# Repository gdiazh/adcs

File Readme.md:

Project: ADCS for SUCHAI CubeSat
--------------------------------------

# Overview

The drivers and interface for SUCHAI CubeSat.

# Content

-[sw]

--[Drivers](#drivers)

--[Interface](#interface)

--[Firmware](#firmware)

-[hw]()

-[Eagle](#eagle)

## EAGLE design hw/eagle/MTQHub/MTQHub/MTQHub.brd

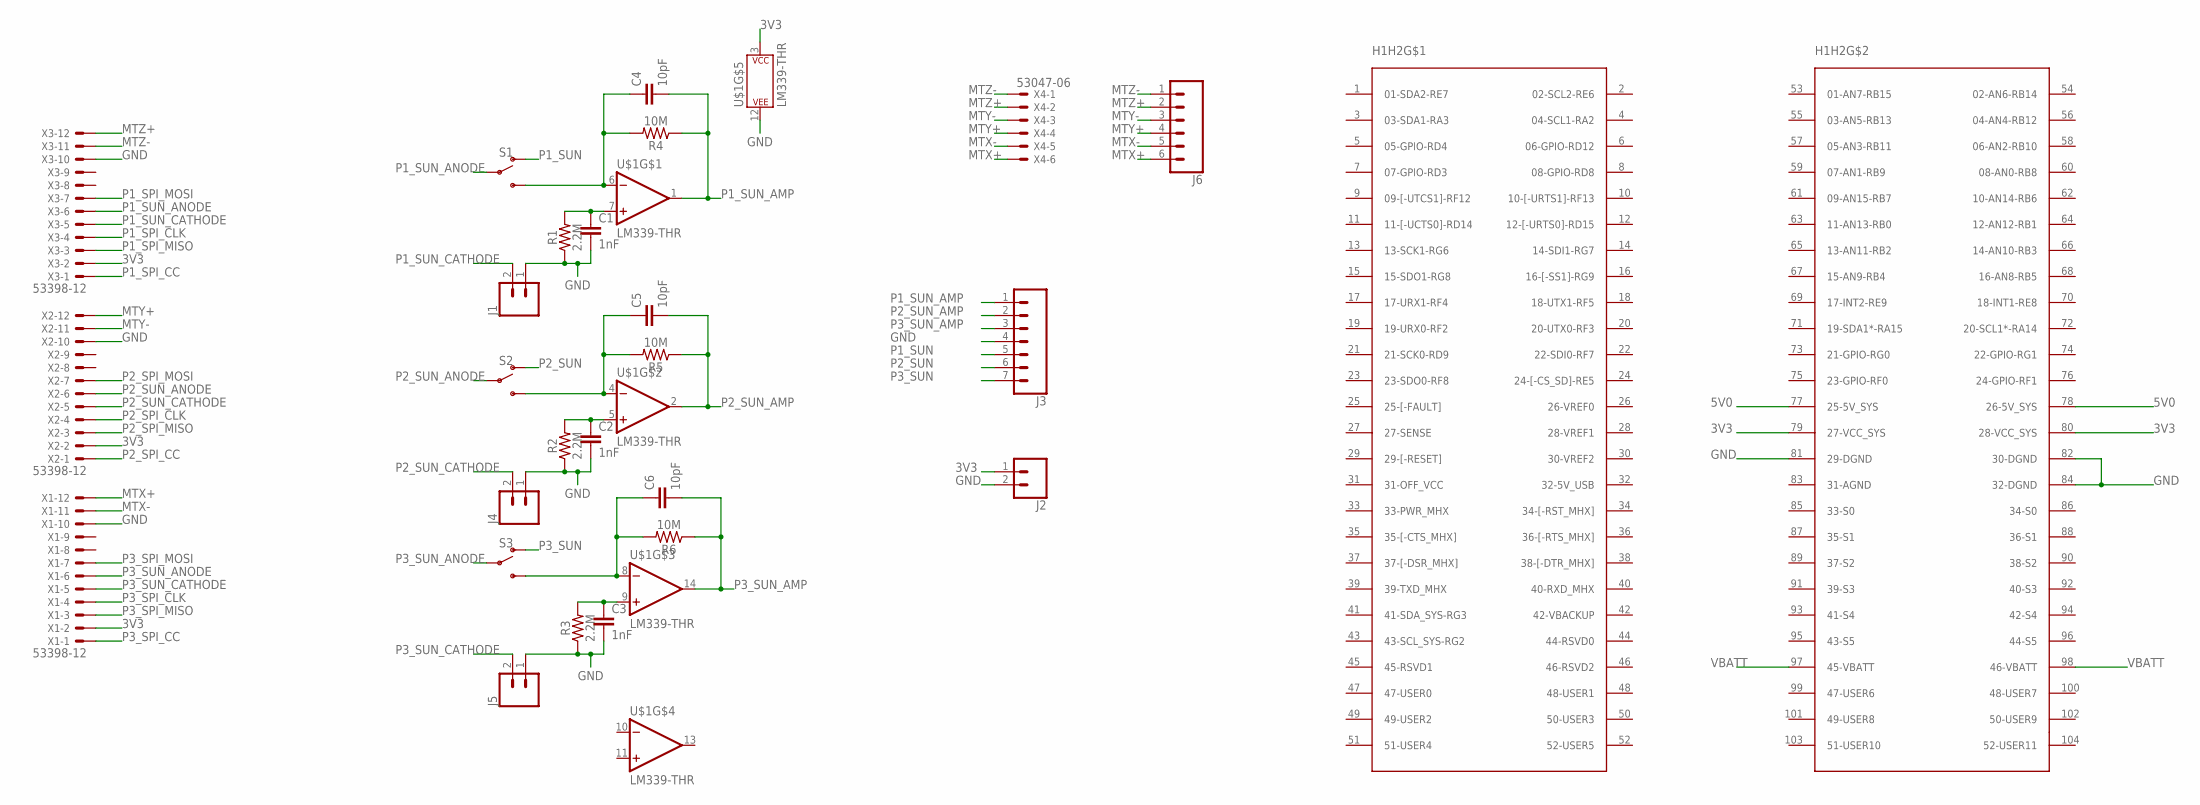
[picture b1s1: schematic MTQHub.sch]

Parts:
C1, C2, C3: 1nF; 0603
C4, C5, C6: 10pF; 0603
H1H2: PC104_CONN; PC_104
J1, J2, J4, J5: CONN_02; 1X02
J3: CONN_07; 1X07
J6: CONN_06SILK_FEMALE_PTH; 1X06
R1, R2, R3: 2.2M; 0603
R4, R5, R6: 10M; 0603
S1, S2, S3: SWITCH-SPDT-PTH-11.6X4.0MM; SWITCH_SPDT_PTH_11.6X4.0MM
U$1: LM339-THR; DIL14
X1, X2, X3: 53398-12
X4: 53047-06

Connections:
3V3: H1H2.79 (27-VCC_SYS), H1H2.80 (28-VCC_SYS), J2.1, U$1.3 (P$V+), X1.2, X2.2, X3.2
5V0: H1H2.77 (25-5V_SYS), H1H2.78 (26-5V_SYS)
GND: C1.2, C2.2, C3.2, H1H2.81 (29-DGND), H1H2.82 (30-DGND), H1H2.84 (32-DGND), J1.1, J2.2, J3.4, J4.1, J5.1, R1.1, R2.1, R3.1, U$1.12 (P$V-), X1.10, X2.10, X3.10
MTX+: J6.6, X1.12, X4.6
MTX-: J6.5, X1.11, X4.5
MTY+: J6.4, X2.12, X4.4
MTY-: J6.3, X2.11, X4.3
MTZ+: J6.2, X3.12, X4.2
MTZ-: J6.1, X3.11, X4.1
unnamed: C1.1, R1.2, U$1.7 (+IN)
unnamed: C2.1, R2.2, U$1.5 (+IN)
unnamed: C3.1, R3.2, U$1.9 (+IN)
unnamed: C4.1, R4.2, S1.3 (S), U$1.6 (-IN)
unnamed: C5.1, R5.2, S2.3 (S), U$1.4 (-IN)
unnamed: C6.1, R6.2, S3.3 (S), U$1.8 (-IN)
P1_SPI_CC: X3.1
P1_SPI_CLK: X3.4
P1_SPI_MISO: X3.3
P1_SPI_MOSI: X3.7
P1_SUN: J3.5, S1.1 (O)
P1_SUN_AMP: C4.2, J3.1, R4.1, U$1.1 (OUT)
P1_SUN_ANODE: S1.2, X3.6
P1_SUN_CATHODE: J1.2, X3.5
P2_SPI_CC: X2.1
P2_SPI_CLK: X2.4
P2_SPI_MISO: X2.3
P2_SPI_MOSI: X2.7
P2_SUN: J3.6, S2.1 (O)
P2_SUN_AMP: C5.2, J3.2, R5.1, U$1.2 (OUT)
P2_SUN_ANODE: S2.2, X2.6
P2_SUN_CATHODE: J4.2, X2.5
P3_SPI_CC: X1.1
P3_SPI_CLK: X1.4
P3_SPI_MISO: X1.3
P3_SPI_MOSI: X1.7
P3_SUN: J3.7, S3.1 (O)
P3_SUN_AMP: C6.2, J3.3, R6.1, U$1.14 (OUT)
P3_SUN_ANODE: S3.2, X1.6
P3_SUN_CATHODE: J5.2, X1.5
VBATT: H1H2.97 (45-VBATT), H1H2.98 (46-VBATT)

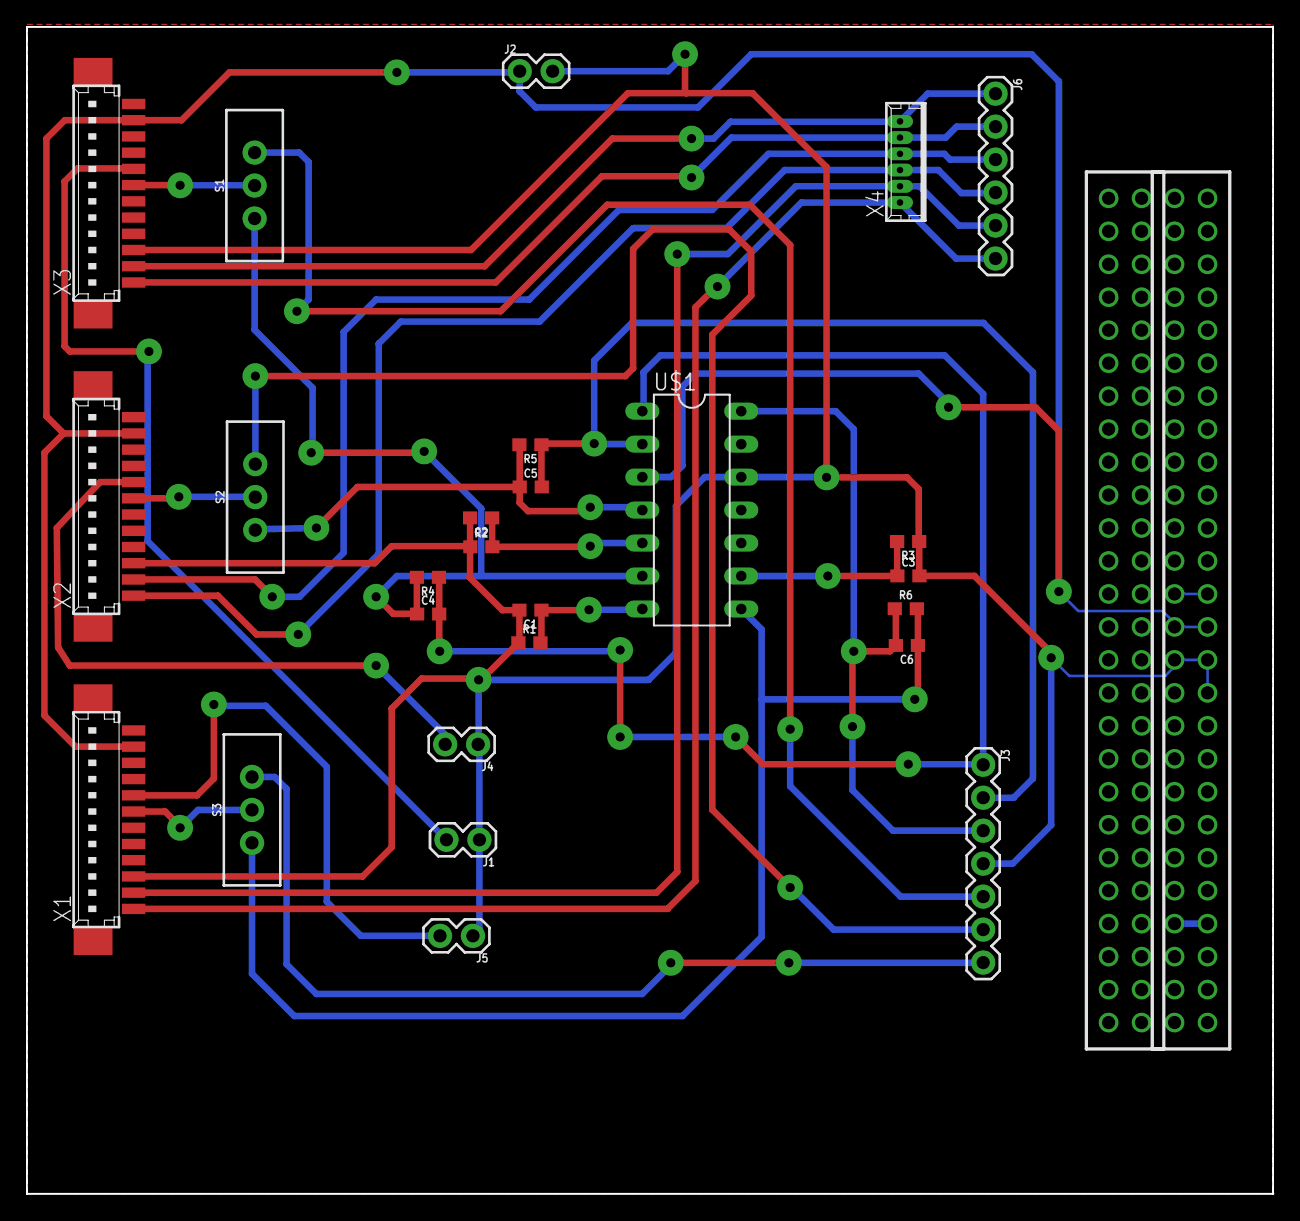
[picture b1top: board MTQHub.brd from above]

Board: 2 copper layers, 96.0 x 89.9 mm, 27 parts (0 on the bottom side), 28 nets.

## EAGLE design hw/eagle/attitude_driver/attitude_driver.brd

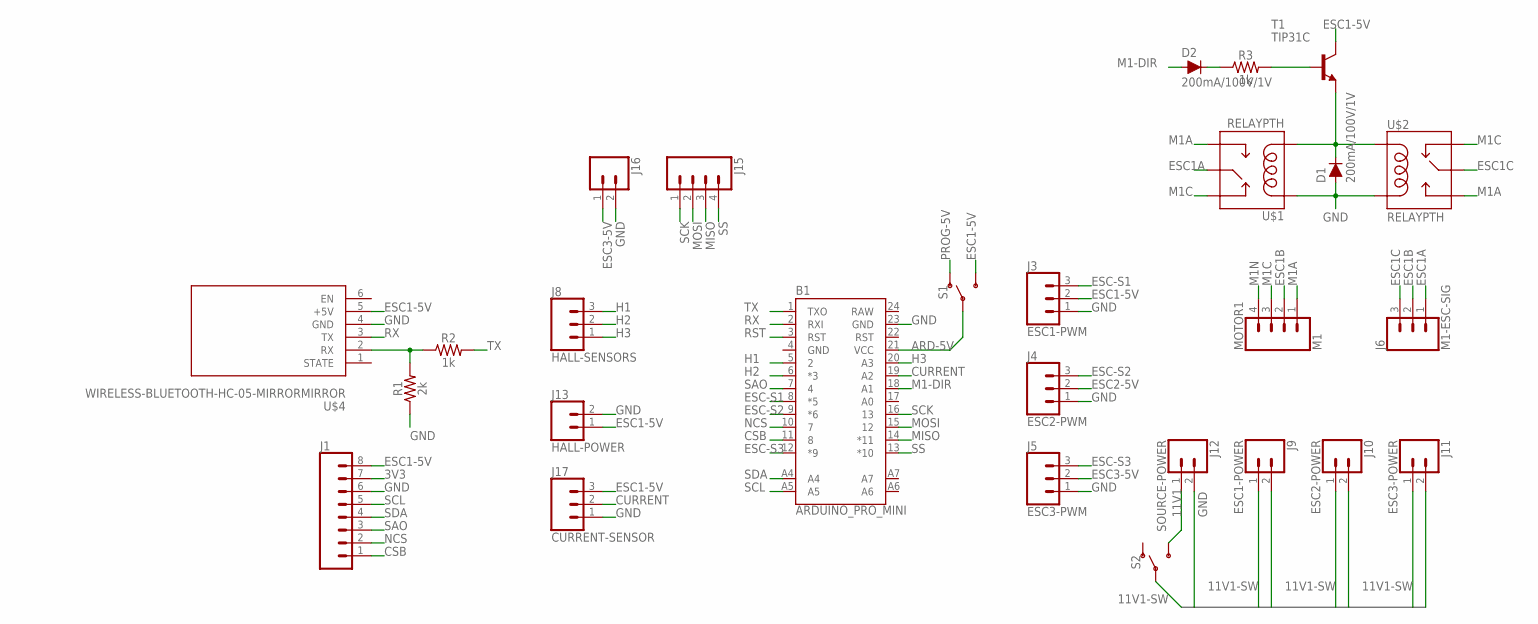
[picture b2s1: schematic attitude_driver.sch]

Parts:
B1: ARDUINO_PRO_MINI
D1, D2: 200mA/100V/1V; DIODE-1N4148
J1: GY-91LOCK_LONGPADS; GY91_LONGPADS
J3: ESC1-PWM; 1X03_LOCK_LONGPADS
J4: ESC2-PWM; 1X03_LOCK_LONGPADS
J5: ESC3-PWM; 1X03_LOCK_LONGPADS
J6: M1-ESC-SIG; 1X03_LOCK_LONGPADS
J8: HALL-SENSORS; 1X03_LOCK_LONGPADS
J9: ESC1-POWER; 1X02_LOCK_LONGPADS
J10: ESC2-POWER; 1X02_LOCK_LONGPADS
J11: ESC3-POWER; 1X02_LOCK_LONGPADS
J12: SOURCE-POWER; 1X02_LOCK_LONGPADS
J13: HALL-POWER; 1X02_LOCK_LONGPADS
J15: CONN_04LOCK_LONGPADS; 1X04_LOCK_LONGPADS
J16: CONN_02LOCK_LONGPADS; 1X02_LOCK_LONGPADS
J17: CURRENT-SENSOR; 1X03_LOCK_LONGPADS
MOTOR1: M1; 1X04_LOCK_LONGPADS
R1: 2k; AXIAL-0.3
R2, R3: 1k; AXIAL-0.3
S1, S2: SWITCH-SPDT-PTH-11.6X4.0MM-LOCK; SWITCH_SPDT_PTH_11.6X4.0MM_LOCK
T1: TIP31C; TO220
U$1, U$2: RELAYPTH; SRD-05VDC-SL-C
U$4: WIRELESS-BLUETOOTH-HC-05-MIRRORMIRROR; WIRELESS-BLUETOOTH-HC-05-MIRROR

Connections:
3V3: J1.7
11V1: J12.1, S2.3 (S)
11V1-SW: J9.1, J10.1, J11.1, S2.2
ARD-5V: B1.21 (VCC), S1.2
CSB: B1.11 (8), J1.1
CURRENT: B1.19 (A2), J17.2
ESC1-5V: J1.8, J3.2, J13.1, J17.3, S1.3 (S), T1.2 (C), U$4.5 (+5V)
ESC1A: J6.1, U$1.SWCOMMON
ESC1B: J6.2, MOTOR1.2
ESC1C: J6.3, U$2.SWCOMMON
ESC2-5V: J4.2
ESC3-5V: J5.2, J16.1
ESC-S1: B1.8 (*5), J3.3
ESC-S2: B1.9 (*6), J4.3
ESC-S3: B1.12 (*9), J5.3
GND: B1.4 (GND), B1.23 (GND), D1.A, J1.6, J3.1, J4.1, J5.1, J9.2, J10.2, J11.2, J12.2, J13.2, J16.2, J17.1, R1.P$1 (1), U$1.COIL1, U$2.COIL0, U$4.4 (GND)
H1: B1.5 (2), J8.3
H2: B1.6 (*3), J8.2
H3: B1.20 (A3), J8.1
M1-DIR: B1.18 (A1), D2.A
M1A: MOTOR1.1, U$1.SWOPEN, U$2.SWOPEN
M1C: MOTOR1.3, U$1.SWCLOSED (SWCLOSE), U$2.SWCLOSED (SWCLOSE)
M1N: MOTOR1.4
MISO: B1.14 (*11), J15.3
MOSI: B1.15 (12), J15.2
unnamed: R1.P$2 (2), R2.P$1 (1), U$4.2 (RX)
unnamed: R3.P$2 (2), T1.1 (B)
unnamed: D2.C, R3.P$1 (1)
unnamed: D1.C, T1.3 (E), U$1.COIL0, U$2.COIL1
NCS: B1.10 (7), J1.2
PROG-5V: S1.1 (O)
RAW: B1.24 (RAW)
RST: B1.3 (RST)
RX: B1.2 (RXI), U$4.3 (TX)
SAO: B1.7 (4), J1.3
SCK: B1.16 (13), J15.1
SCL: B1.A5, J1.5
SDA: B1.A4, J1.4
SS: B1.13 (*10), J15.4
TX: B1.1 (TXO), R2.P$2 (2)

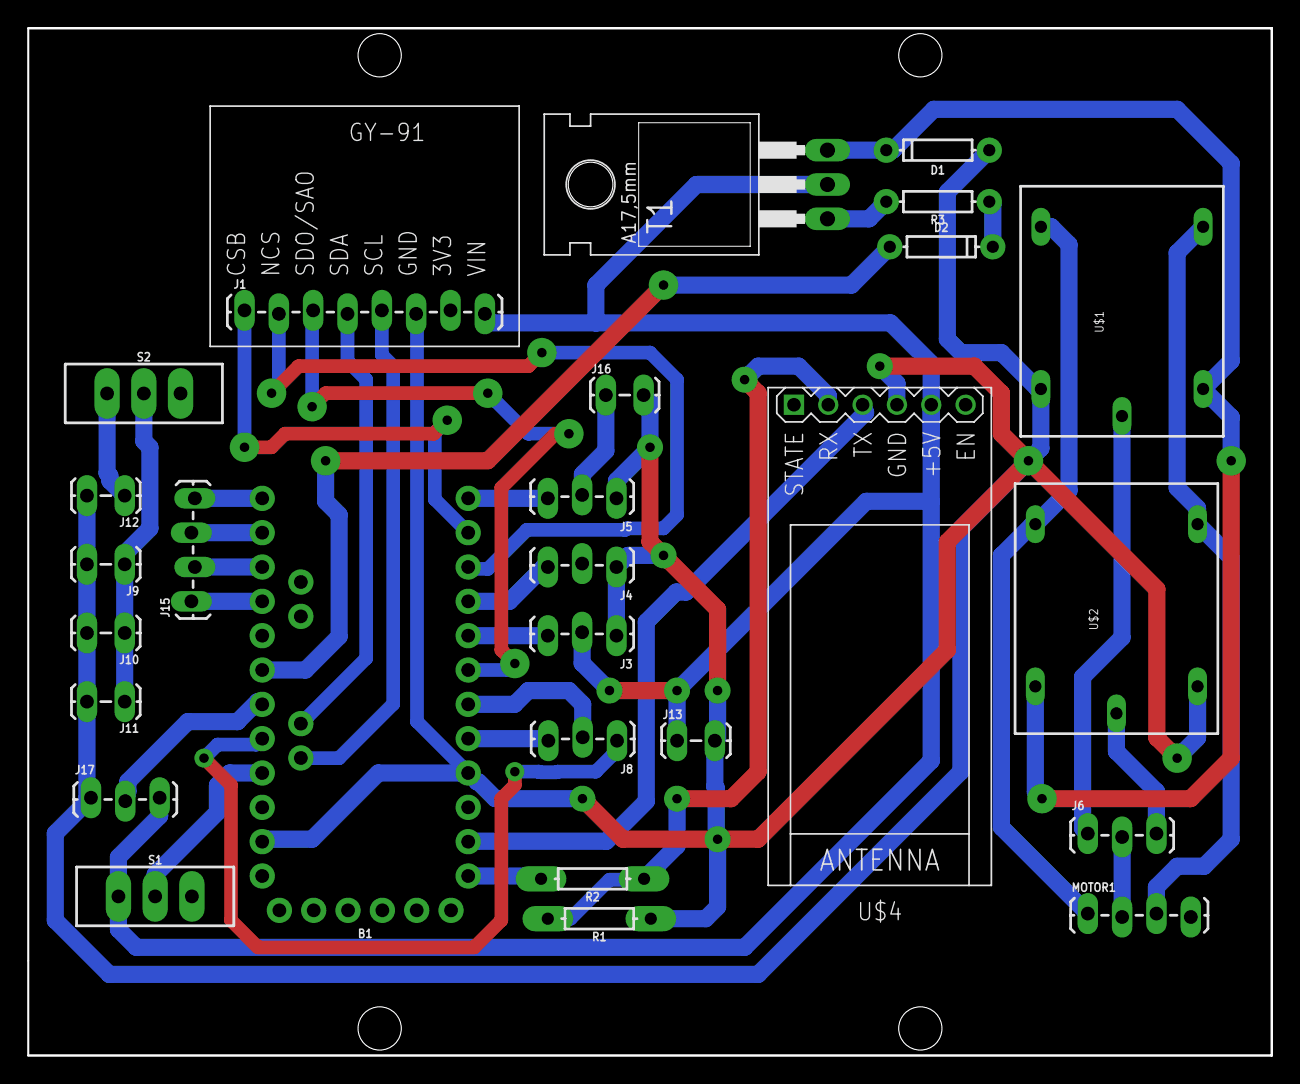
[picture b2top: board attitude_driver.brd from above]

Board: 2 copper layers, 92.0 x 76.0 mm, 27 parts (0 on the bottom side), 34 nets.

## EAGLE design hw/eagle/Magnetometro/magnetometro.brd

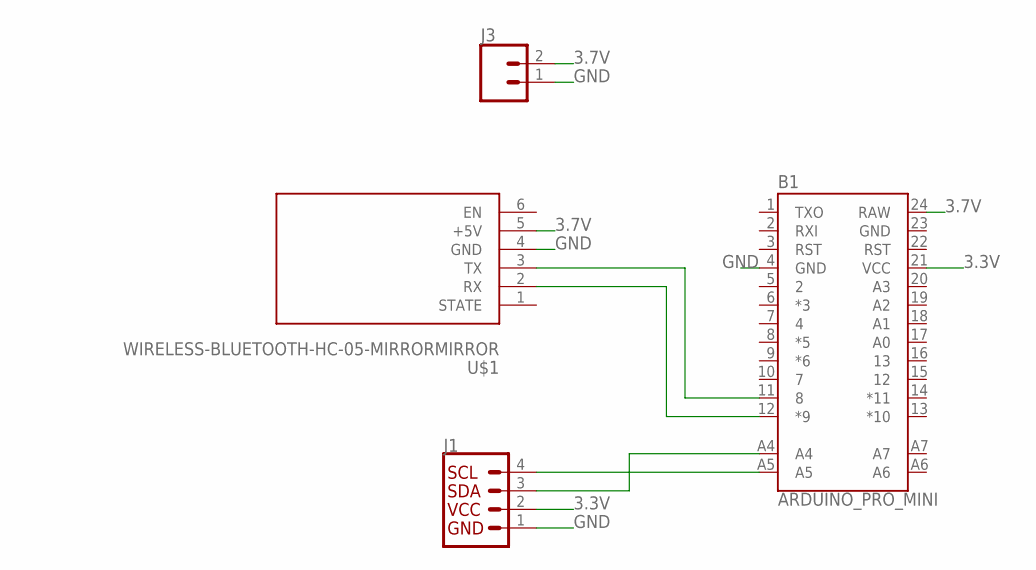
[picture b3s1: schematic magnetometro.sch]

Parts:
B1: ARDUINO_PRO_MINI
J1: I2C_STANDARD; 1X04
J3: CONN_02-JST-2-PTH-NO_SILK; JST-2-PTH-NS
U$1: WIRELESS-BLUETOOTH-HC-05-MIRRORMIRROR; WIRELESS-BLUETOOTH-HC-05-MIRROR

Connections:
3.3V: B1.21 (VCC), J1.2
3.7V: B1.24 (RAW), J3.2, U$1.5 (+5V)
GND: B1.4 (GND), B1.23 (GND), J1.1, J3.1, U$1.4 (GND)
unnamed: B1.11 (8), U$1.3 (TX)
unnamed: B1.12 (*9), U$1.2 (RX)
unnamed: B1.A5, J1.4
unnamed: B1.A4, J1.3

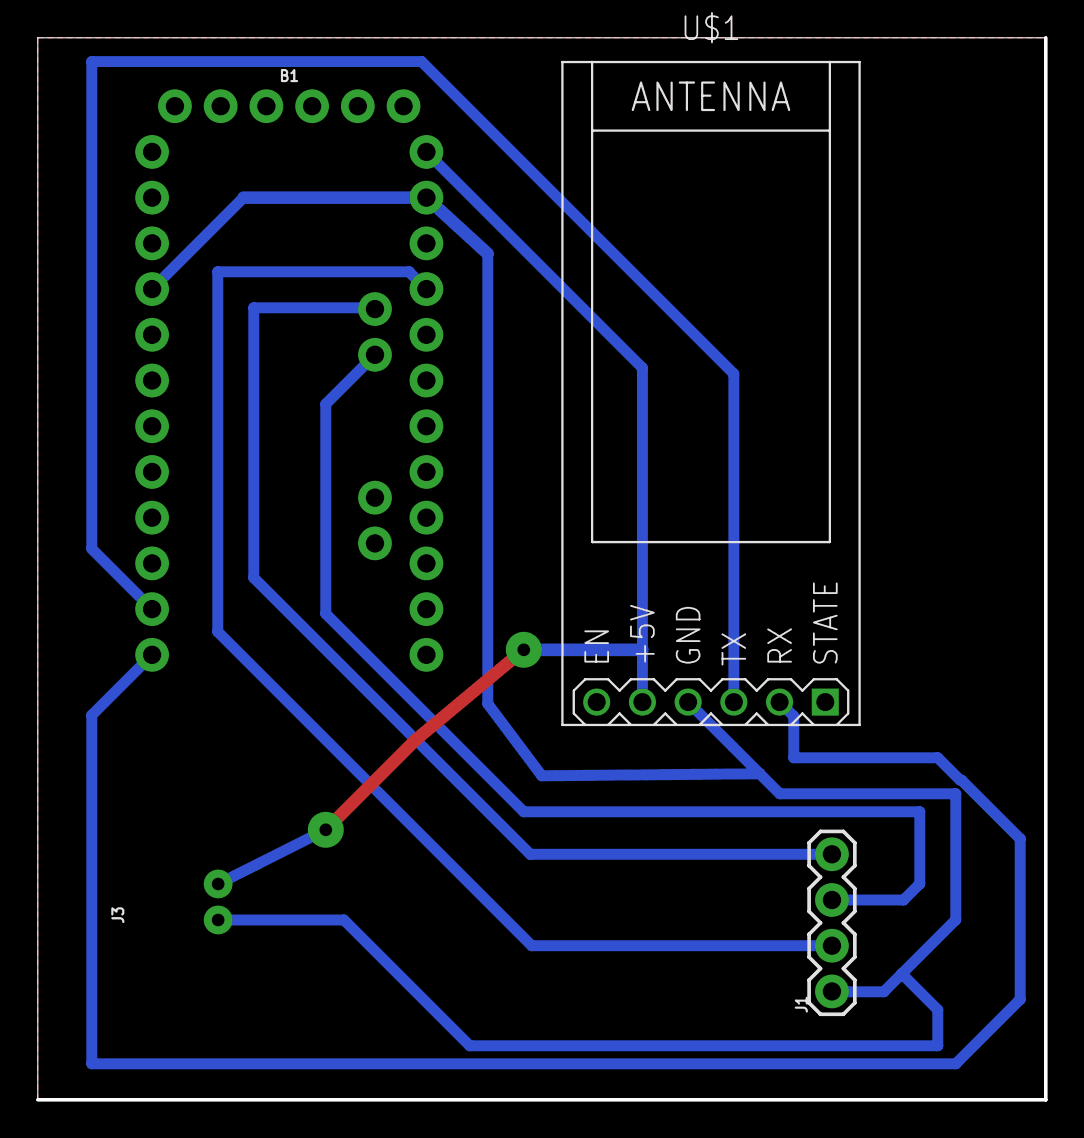
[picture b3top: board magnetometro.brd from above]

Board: 2 copper layers, 56.0 x 59.0 mm, 4 parts (0 on the bottom side), 7 nets.

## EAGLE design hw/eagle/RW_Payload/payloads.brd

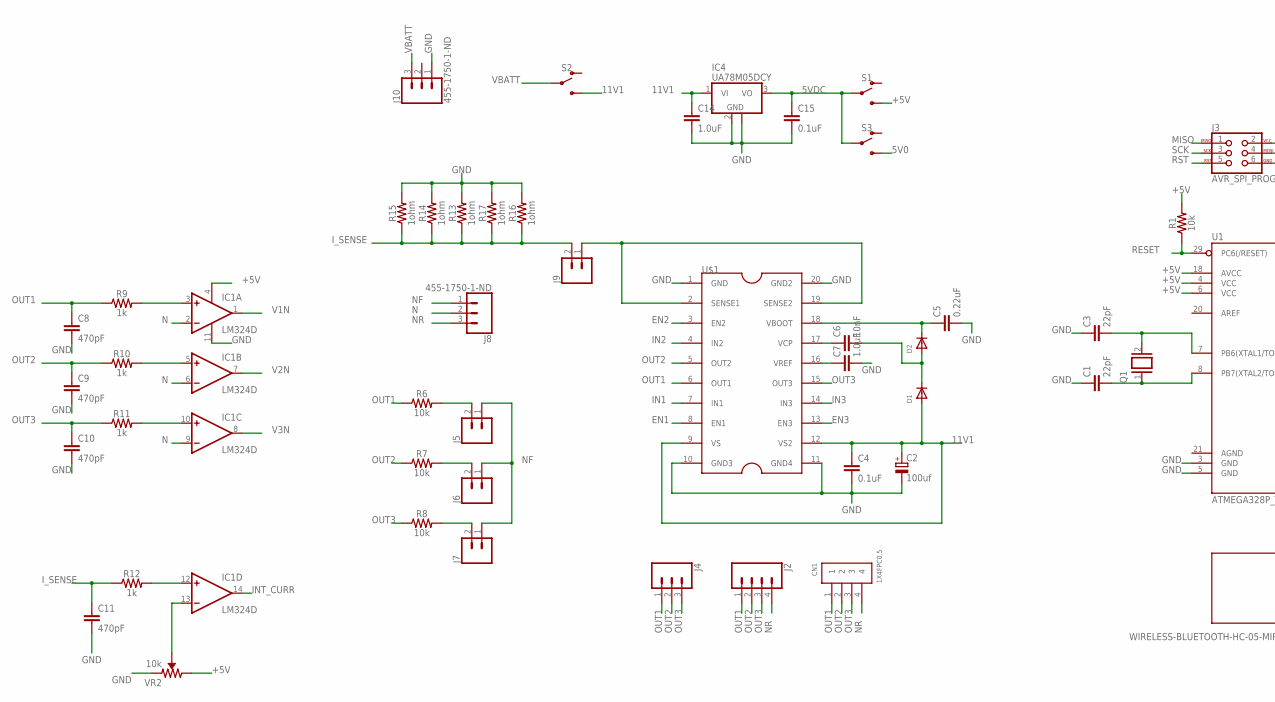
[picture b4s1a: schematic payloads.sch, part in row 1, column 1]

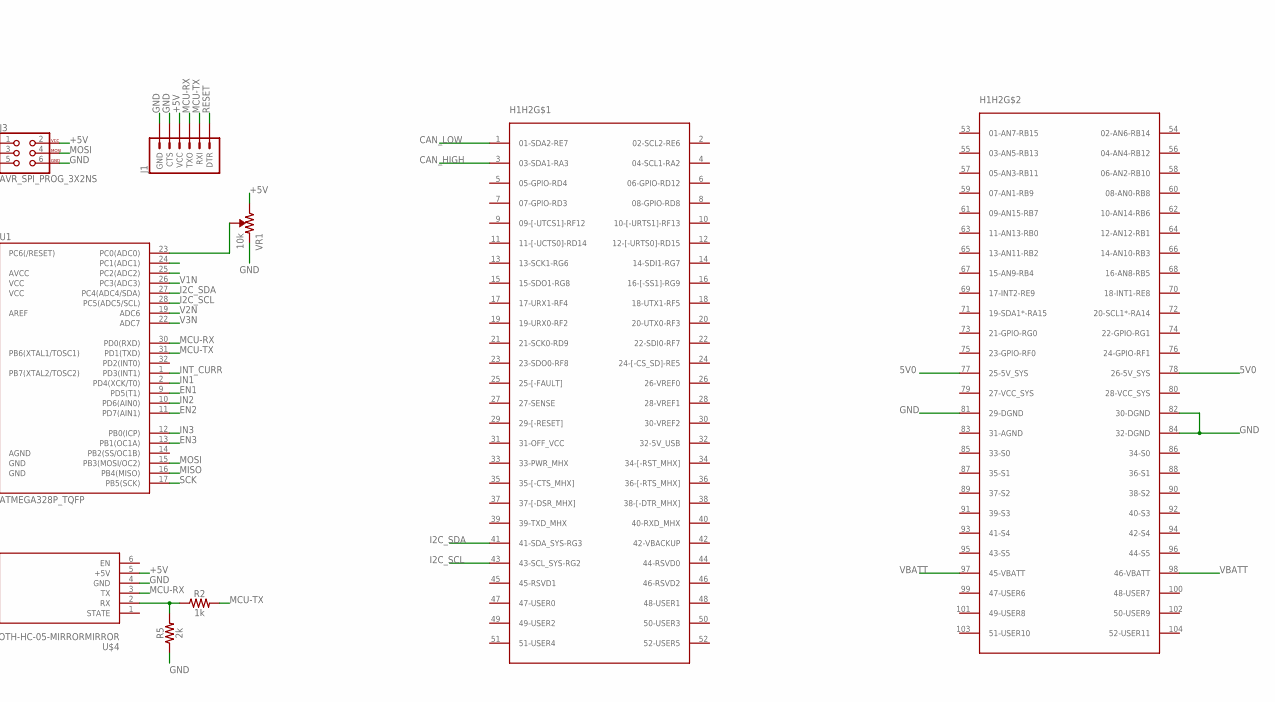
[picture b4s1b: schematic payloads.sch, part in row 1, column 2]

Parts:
C1, C3: 22pF; 1206
C2: 100uf; C/6032-28R
C4: 0.1uF; 0603
C5: 0.22uF; 0603
C6: 10nF; 0603
C7: 1.0uF; 0603
C8, C9, C10, C11: 470pF; 0603
C14: 1.0uF; 1206
C15: 0.1uF; 1206
CN1: 1X4FPC0.5; FPC_0.5MM-4
D1, D2: DIODESOD-123; SOD-123
H1H2: PC104_CONN; PC_104
IC1: LM324D; SO14
IC4: UA78M05DCY; SOT223
J1: 6_PIN_SERIAL_TARGET; 1X06
J2: CONN_04; 1X04
J3: AVR_SPI_PROG_3X2NS; 2X3-NS
J4: CONN_03-SCREW-5MM; SCREWTERMINAL-5MM-3
J5, J6, J7, J9: CONN_02; 1X02
J8, J10: 455-1750-1-ND; 1X03
Q1: XTAL/S; QS
R1: 10k; 1206
R2: 1k; AXIAL-0.3
R5: 2k; AXIAL-0.3
R6, R7, R8: 10k; AXIAL-0.3
R9, R10, R11, R12: 1k; 0603
R13, R14, R15, R16, R17: 1ohm; AXIAL-0.3
S1, S2, S3: SWITCH-SPDT-PTH-11.6X4.0MM; SWITCH_SPDT_PTH_11.6X4.0MM
U1: ATMEGA328P_TQFP; TQFP32-08
U$1: L6234PD; SO20
U$4: WIRELESS-BLUETOOTH-HC-05-MIRRORMIRROR; WIRELESS-BLUETOOTH-HC-05-MIRROR
VR1, VR2: 10k; TRIMPOT-PTH-3386U

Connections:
5V0: H1H2.77 (25-5V_SYS), H1H2.78 (26-5V_SYS), S3.3 (S)
5VDC: C15.1, IC4.3 (VO), S1.2, S3.2
11V1: C2.+, C4.1, C14.1, D1.A, IC4.1 (VI), S2.3 (S), U$1.9 (VS), U$1.12 (VS2)
+5V: IC1.4 (V+), J1.4 (VCC), J3.2, R1.2, S1.3 (S), U1.4 (VCC), U1.6 (VCC), U1.18 (AVCC), U$4.5 (+5V), VR1.3 (CW), VR2.3 (CW)
CAN_HIGH: H1H2.3 (03-SDA1-RA3)
CAN_LOW: H1H2.1 (01-SDA2-RE7)
EN1: U1.9 (PD5(T1)), U$1.8 (EN1)
EN2: U1.11 (PD7(AIN1)), U$1.3 (EN2)
EN3: U1.13 (PB1(OC1A)), U$1.13 (EN3)
GND: C1.1, C2.-, C3.1, C4.2, C5.2, C7.2, C8.2, C9.2, C10.2, C11.2, C14.2, C15.2, H1H2.81 (29-DGND), H1H2.82 (30-DGND), H1H2.84 (32-DGND), IC1.11 (V-), IC4.2 (GND), IC4.4 (GND), J1.5 (CTS), J1.6 (GND), J3.6, J10.1, R5.P$1 (1), R13.P$2 (2), R14.P$2 (2), R15.P$2 (2), R16.P$2 (2), R17.P$2 (2), U1.3 (GND), U1.5 (GND), U$1.1 (GND), U$1.10 (GND3), U$1.11 (GND4), U$1.20 (GND2), U$4.4 (GND), VR1.1 (CCW), VR2.1 (CCW)
I2C_SCL: H1H2.43 (43-SCL_SYS-RG2), U1.28 (PC5(ADC5/SCL))
I2C_SDA: H1H2.41 (41-SDA_SYS-RG3), U1.27 (PC4(ADC4/SDA))
IN1: U1.2 (PD4(XCK/T0)), U$1.7 (IN1)
IN2: U1.10 (PD6(AIN0)), U$1.4 (IN2)
IN3: U1.12 (PB0(ICP)), U$1.14 (IN3)
INT_CURR: IC1.14 (OUT), U1.1 (PD3(INT1))
I_SENSE: C11.1, J9.2, R12.1, R13.P$1 (1), R14.P$1 (1), R15.P$1 (1), R16.P$1 (1), R17.P$1 (1)
MCU-RX: J1.3 (TXO), U1.30 (PD0(RXD)), U$4.3 (TX)
MCU-TX: J1.2 (RXI), R2.P$2 (2), U1.31 (PD1(TXD))
MISO: J3.1, U1.16 (PB4(MISO))
MOSI: J3.4, U1.15 (PB3(MOSI/OC2))
N: IC1.2 (-IN), IC1.6 (-IN), IC1.9 (-IN), J8.2
unnamed: C3.2, Q1.2, U1.7 (PB6(XTAL1/TOSC1))
unnamed: C1.2, Q1.1, U1.8 (PB7(XTAL2/TOSC2))
unnamed: R2.P$1 (1), R5.P$2 (2), U$4.2 (RX)
unnamed: C6.1, U$1.17 (VCP)
unnamed: C6.2, D1.C, D2.A
unnamed: C5.1, D2.C, U$1.18 (VBOOT)
unnamed: IC1.13 (-IN), VR2.2 (WIPER)
unnamed: U1.23 (PC0(ADC0)), VR1.2 (WIPER)
unnamed: C7.1, U$1.16 (VREF)
unnamed: IC1.3 (+IN), R9.2
unnamed: J5.2, R6.P$2 (2)
unnamed: J6.2, R7.P$2 (2)
unnamed: J7.2, R8.P$2 (2)
unnamed: IC1.5 (+IN), R10.2
unnamed: IC1.10 (+IN), R11.2
unnamed: IC1.12 (+IN), R12.2
unnamed: J9.1, U$1.2 (SENSE1), U$1.19 (SENSE2)
NF: J5.1, J6.1, J7.1, J8.1
NR: CN1.4, J2.4, J8.3
OUT1: C8.1, CN1.1, J2.1, J4.1, R6.P$1 (1), R9.1, U$1.6 (OUT1)
OUT2: C9.1, CN1.2, J2.2, J4.2, R7.P$1 (1), R10.1, U$1.5 (OUT2)
OUT3: C10.1, CN1.3, J2.3, J4.3, R8.P$1 (1), R11.1, U$1.15 (OUT3)
RESET: J1.1 (DTR), R1.1, U1.29 (PC6(/RESET))
RST: J3.5
SCK: J3.3, U1.17 (PB5(SCK))
V1N: IC1.1 (OUT), U1.26 (PC3(ADC3))
V2N: IC1.7 (OUT), U1.19 (ADC6)
V3N: IC1.8 (OUT), U1.22 (ADC7)
VBATT: H1H2.97 (45-VBATT), H1H2.98 (46-VBATT), J10.3, S2.2

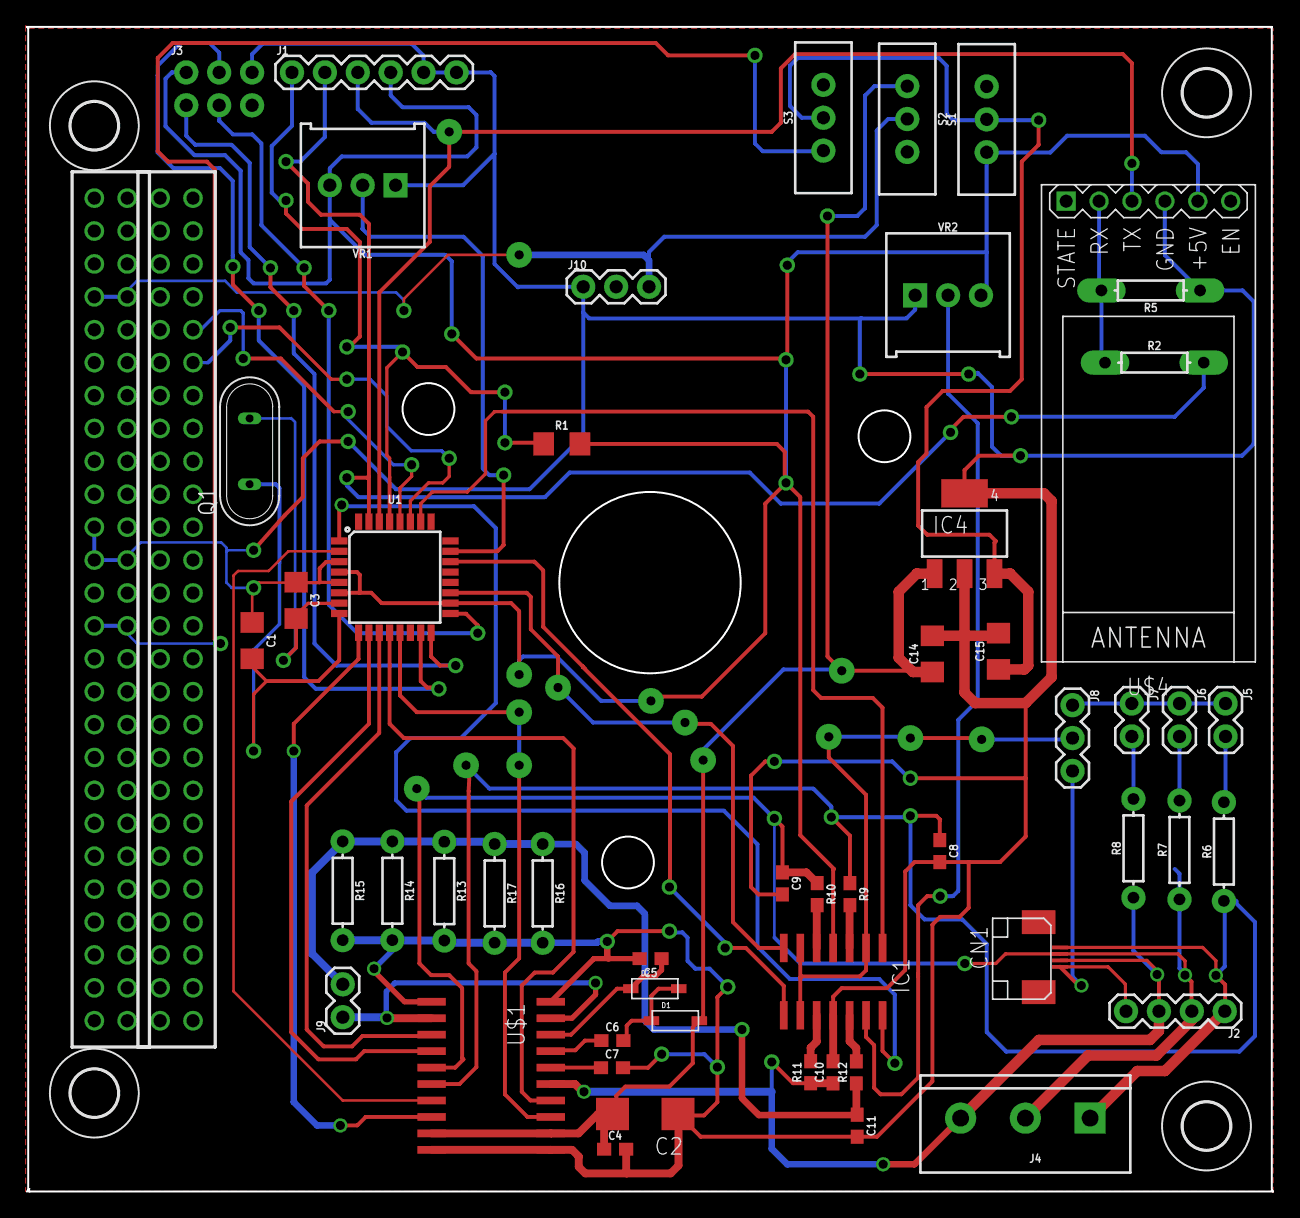
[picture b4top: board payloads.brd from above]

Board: 2 copper layers, 96.2 x 89.9 mm, 57 parts (0 on the bottom side), 48 nets.

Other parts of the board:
U$11, U$12, U$13, U$14: 3,6

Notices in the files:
parts and their libraries:
SparkFun-Connectors: Licensing: Creative Commons ShareAlike 4.0 International - https://creativecommons.org/licenses/by-sa/4.0
diy-modules: Released under the Creative Commons Attribution 4.0 International License: http://creativecommons.org/licenses/by/4.0
